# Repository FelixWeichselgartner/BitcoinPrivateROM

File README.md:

Save your private keys on a diode ROM array

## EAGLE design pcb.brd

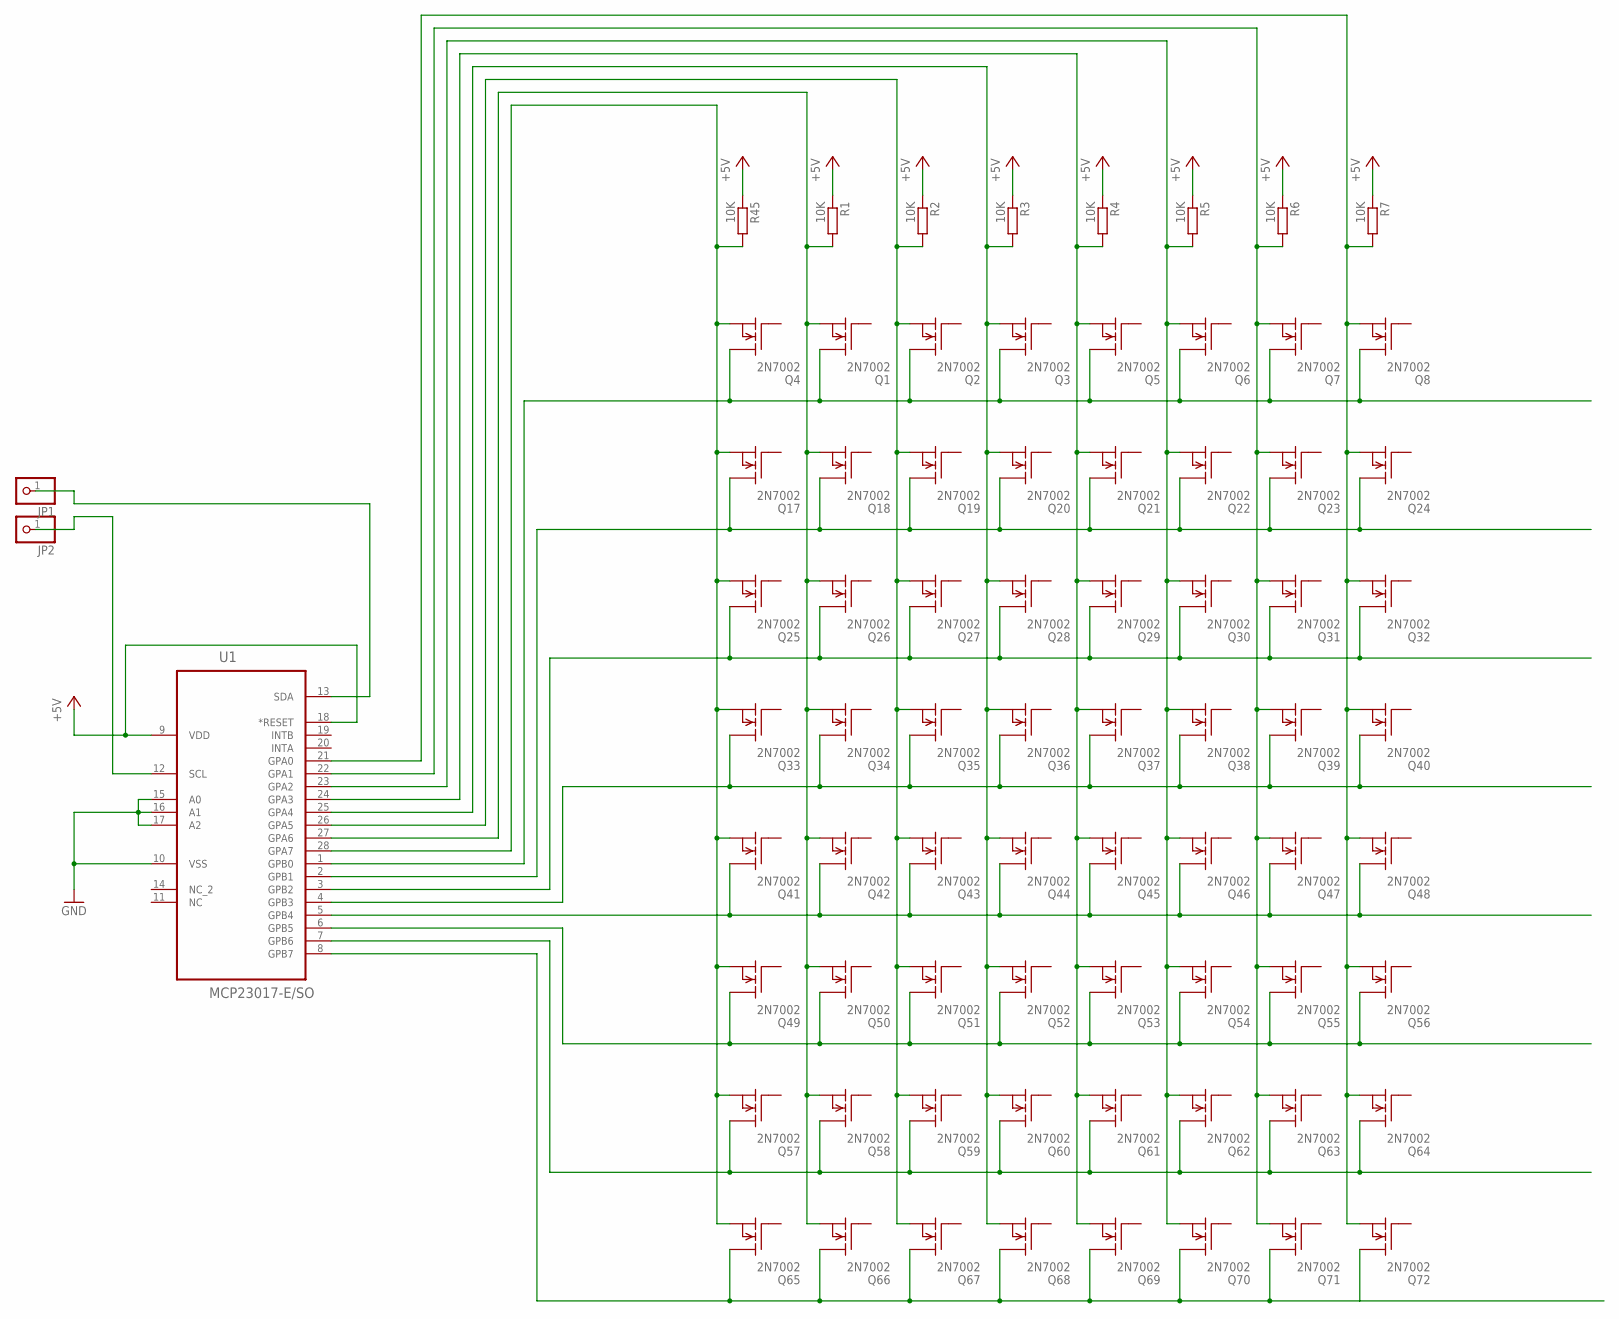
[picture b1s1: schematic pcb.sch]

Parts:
JP1, JP2: PINHD-1X1; 1X01
Q1, Q2, Q3, Q4, Q5, Q6, Q7, Q8, Q17, Q18, Q19, Q20, Q21, Q22, Q23, Q24, Q25, Q26, Q27, Q28, Q29, Q30, Q31, Q32, Q33, Q34, Q35, Q36, Q37, Q38, Q39, Q40, Q41, Q42, Q43, Q44, Q45, Q46, Q47, Q48, Q49, Q50, Q51, Q52, Q53, Q54, Q55, Q56, Q57, Q58, Q59, Q60, Q61, Q62, Q63, Q64, Q65, Q66, Q67, Q68, Q69, Q70, Q71, Q72: 2N7002; SOT23
R1, R2, R3, R4, R5, R6, R7, R45: 10K; R0805
U1: MCP23017-E/SO; SOIC127P1032X265-28N

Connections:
+5V: R1.1, R2.1, R3.1, R4.1, R5.1, R6.1, R7.1, R45.1, U1.9 (VDD), U1.18 (*RESET)
GND: U1.10 (VSS), U1.15 (A0), U1.16 (A1), U1.17 (A2)
unnamed: Q1.3 (D), Q2.3 (D), Q3.3 (D), Q4.3 (D), Q5.3 (D), Q6.3 (D), Q7.3 (D), Q8.3 (D), U1.1 (GPB0)
unnamed: JP2.1, U1.12 (SCL)
unnamed: Q57.3 (D), Q58.3 (D), Q59.3 (D), Q60.3 (D), Q61.3 (D), Q62.3 (D), Q63.3 (D), Q64.3 (D), U1.7 (GPB6)
unnamed: Q17.3 (D), Q18.3 (D), Q19.3 (D), Q20.3 (D), Q21.3 (D), Q22.3 (D), Q23.3 (D), Q24.3 (D), U1.2 (GPB1)
unnamed: Q25.3 (D), Q26.3 (D), Q27.3 (D), Q28.3 (D), Q29.3 (D), Q30.3 (D), Q31.3 (D), Q32.3 (D), U1.3 (GPB2)
unnamed: Q33.3 (D), Q34.3 (D), Q35.3 (D), Q36.3 (D), Q37.3 (D), Q38.3 (D), Q39.3 (D), Q40.3 (D), U1.4 (GPB3)
unnamed: Q41.3 (D), Q42.3 (D), Q43.3 (D), Q44.3 (D), Q45.3 (D), Q46.3 (D), Q47.3 (D), Q48.3 (D), U1.5 (GPB4)
unnamed: Q49.3 (D), Q50.3 (D), Q51.3 (D), Q52.3 (D), Q53.3 (D), Q54.3 (D), Q55.3 (D), Q56.3 (D), U1.6 (GPB5)
unnamed: Q4.2 (S), Q17.2 (S), Q25.2 (S), Q33.2 (S), Q41.2 (S), Q49.2 (S), Q57.2 (S), Q65.2 (S), R45.2, U1.28 (GPA7)
unnamed: Q1.2 (S), Q18.2 (S), Q26.2 (S), Q34.2 (S), Q42.2 (S), Q50.2 (S), Q58.2 (S), Q66.2 (S), R1.2, U1.27 (GPA6)
unnamed: Q2.2 (S), Q19.2 (S), Q27.2 (S), Q35.2 (S), Q43.2 (S), Q51.2 (S), Q59.2 (S), Q67.2 (S), R2.2, U1.26 (GPA5)
unnamed: Q3.2 (S), Q20.2 (S), Q28.2 (S), Q36.2 (S), Q44.2 (S), Q52.2 (S), Q60.2 (S), Q68.2 (S), R3.2, U1.25 (GPA4)
unnamed: Q5.2 (S), Q21.2 (S), Q29.2 (S), Q37.2 (S), Q45.2 (S), Q53.2 (S), Q61.2 (S), Q69.2 (S), R4.2, U1.24 (GPA3)
unnamed: Q6.2 (S), Q22.2 (S), Q30.2 (S), Q38.2 (S), Q46.2 (S), Q54.2 (S), Q62.2 (S), Q70.2 (S), R5.2, U1.23 (GPA2)
unnamed: Q7.2 (S), Q23.2 (S), Q31.2 (S), Q39.2 (S), Q47.2 (S), Q55.2 (S), Q63.2 (S), Q71.2 (S), R6.2, U1.22 (GPA1)
unnamed: Q8.2 (S), Q24.2 (S), Q32.2 (S), Q40.2 (S), Q48.2 (S), Q56.2 (S), Q64.2 (S), Q72.2 (S), R7.2, U1.21 (GPA0)
unnamed: Q65.3 (D), Q66.3 (D), Q67.3 (D), Q68.3 (D), Q69.3 (D), Q70.3 (D), Q71.3 (D), Q72.3 (D), U1.8 (GPB7)
SDA_OUT: JP1.1, U1.13 (SDA)

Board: 2 copper layers, 75 parts (0 on the bottom side), 20 nets, no tracks yet.
